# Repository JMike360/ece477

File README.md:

# ece477
Purdue ECE senior design project of team 8 for Fall 2020  
  
## Team members
John Michael Bolinder (Team leader, software engineer, systems engineer)  
Ethan Rodriguez (Systems engineer, secondary software engineer)  
Jiahui Zhu (Software engineer, secondary hardware engineer)  
Andrew Gan (Hardware engineer, secondary systems engineer)  

## Overview
Skeleton Key is a convenient, fully-featured password management solution, completely client-side with no dependence on a cloud service provider or network connection. The device utilizes an ESP32 microcontroller and onboard peripherals to manage encrypted-at-rest password storage, fingerprint-based authentication for easy and secure access to passwords, and interfaces with a client desktop app to wirelessly retrieve passwords via bluetooth or retrieve passwords through a wired USB connection. Passwords transmitted by USB or Bluetooth are encrypted in-flight, and the desktop application provides easy access to passwords on the target user device.
  
## Tools used
USB URT module  
ESP32  
Fingerprint reader  
SD card  
SD card reader  
LCD module  
  
## GPIO table
| GPIO PIN      | Function  | Endpoint     |
|---------------|-----------|--------------|
| 1             | U0TXD     | FT232 RXD    |
| 3             | U0RXD     | FT232 TXD    |
| 9             | U1RXD     | Console in   |
| 10            | U1TXD     | Console_out  |
| 12            | HSPI_MISO | MicroSD Dout |
| 13            | HSPI_MOSI | MicroSD Din  |
| 14            | HSPI_CLK  | MicroSD CLK  |
| 15            | HSPI_CS0  | MicroSD CS   |
| 16            | U2RXD     | Fingerprint Scanner TX |
| 17            | U2TXD     | Fingerprint Scanner RX |
  
UART 0: console/debug  
UART 1: ESP32 - GUI  
UART 2: ESP32 - Fingerprint  
  
GPIO 6-11 - SPI flash  
GPIO 34-39 - input mode only    
[Full layout](https://microcontrollerslab.com/wp-content/uploads/2019/02/ESP32-pinout-mapping.png)  
ESP32 tech ref manual page 57-58  
  
## References
[ESP32 SPI MASTER API](https://docs.espressif.com/projects/esp-idf/en/latest/esp32/api-reference/peripherals/spi_master.html)

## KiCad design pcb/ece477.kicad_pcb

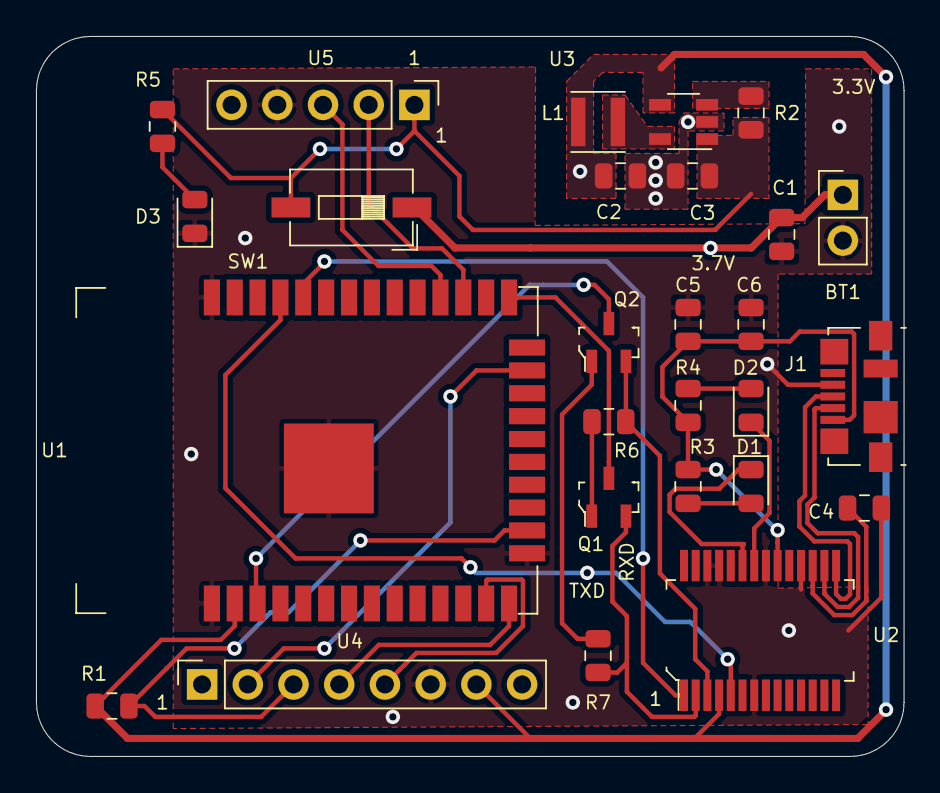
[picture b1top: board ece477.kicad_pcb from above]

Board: 2 copper layers, 48.2 x 40.0 mm, 27 parts (0 on the bottom side), 29 nets.

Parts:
BT1: 3.7V; PinHeader_1x02_P2.54mm_Vertical
C1, C3: 4.7µF; C_0805_2012Metric
C2: 10µF; C_0805_2012Metric
C4, C5: 0.1uF; C_0805_2012Metric
C6: 10uF; C_0805_2012Metric
D1, D2, D3: LED; LED_0805_2012Metric
J1: USB_B; USB_Micro-B_Molex_47346-0001
L1: 2.2µH; IND_LQH3NPN2R2MMEL
Q1, Q2: MMBT2222; SOT-23-3
R1, R2: 10kΩ; R_0805_2012Metric
R3, R4: 500Ω; R_0805_2012Metric
R5, R6, R7: 1kΩ; R_0805_2012Metric
SW1: SW_DIP_x01; SW_DIP_SPSTx01_Slide_6.7x4.1mm_W6.73mm_P2.54mm_LowProfile_J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
U1: ESP32-WROOM-32; ESP32-WROOM-32D
U2: FT232RL-REEL; SSOP-28_W5.30mm
U3: LM3671; TSOT-23-5
U4: ADA254; PinSocket_1x08_P2.54mm_Vertical
U5: ADA751; PinHeader_1x05_P2.54mm_Vertical

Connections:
GND: BT1.2, C1.1, C2.1, C3.1, C4.1, C5.2, C6.2, D3.1, J1.4, U1.1, U1.15, U1.38, U1.39, U2.7, U2.18, U2.21, U2.25, U2.26, U3.2, U4.6, U5.4
unnamed: BT1.1, C1.2, SW1.1
unnamed: C2.2, L1.1, R1.1, U1.2, U2.4, U3.4, U4.7
unnamed: C3.2, R2.2, R5.1, SW1.2, U3.1, U5.1
unnamed: C4.2, U2.17
unnamed: C5.1, C6.1, J1.1, R3.1, R4.1, U2.20
unnamed: D1.1, U2.23
unnamed: D1.2, R3.2
unnamed: D2.1, U2.22
unnamed: D2.2, R4.2
unnamed: D3.2, R5.2
unnamed: J1.2, U2.16
unnamed: J1.3, U2.15
unnamed: L1.2, U3.5
unnamed: Q1.1, R6.1
unnamed: Q1.2, R7.2, U2.2
unnamed: Q1.3, U1.25
unnamed: Q2.1, R7.1
unnamed: Q2.2, R6.2, U2.3
unnamed: Q2.3, U1.3
unnamed: R1.2, U1.16, U4.3
unnamed: R2.1, U3.3
unnamed: U1.13, U4.5
unnamed: U1.14, U4.4
unnamed: U1.23, U4.2
unnamed: U1.27, U5.2
unnamed: U1.28, U5.3
unnamed: U1.34, U2.1
unnamed: U1.35, U2.5

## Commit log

2020-09-03 tidy up README
2020-09-03 added FatFS files
2020-09-03 removed docs
2020-09-03 edit README
2020-09-03 Update README.md
    added new part
2020-09-04 added more references
2020-09-04 added example code
2020-09-04 removed sdinit.jpg
2020-09-05 setup gpio reservation table
2020-09-05 added oled folder
2020-09-05 grouped HSPI buses together
2020-09-06 oled init and cmds
2020-09-06 added pcb
2020-09-07 debug oled
2020-09-07 debug SPI
2020-09-07 removed misc files
2020-09-08 adding oled for SMAT
2020-09-09 used a new way to convert data to SPI ready
2020-09-09 include function to convert uint to SPI format
2020-09-09 added reference
2020-09-15 Update README.md
    Added gpio/pin request
2020-09-15 added fingerprint scanner pins
2020-09-16 template app with crypto tests and uart tests for fingerprint sensor
2020-09-17 sd card init success
2020-09-17 Add files via upload
    Demo Template so far for software application.
    Still need to discuss library and functionality
    Help button will link to user manual,
    Project website will link to the ECE 477 team page.
    Connect Device will help users figure out if their device is connected and if they can access the device from the application.
    User Settings will allow a user to put information, put a their fingerprint (cute gif animation and status bar to be added), and have an emergency pin that will reset the device (maybe)
2020-09-17 Add files via upload
    CORRECT UPLOAD FOLDER
    Demo Template so far for software application.
    Still need to discuss library and functionality
    Help button will link to user manual,
    Project website will link to the ECE 477 team page.
    Connect Device will help users figure out if their device is connected and if they can access the device from the application.
2020-09-18 added sd func
2020-09-18 cleared build files
2020-09-18 connected fingerprint scanner in schematic
2020-09-19 added sd card, battery and esp32 qfn to pcb
2020-09-19 updated pcb
2020-09-19 added wires to pcb
2020-10-06 removed deleteme folder
2020-10-06 Added fingerprint files
2020-10-07 cleanup
2020-10-07 uploaded pcb files
2020-10-08 slight pcb changes
2020-10-08 squeezed lm3671 components together
2020-10-08 pcb update
2020-10-08 shifted LM3671 to top right
2020-10-09 some fixes not done yet
2020-10-09 updated C and R size, fixed LM3671
2020-10-10 connected to ground plate
2020-10-11 added power LED
2020-10-12 fixed LM3671 ground vias
2020-10-14 updated pcb pinheader width
2020-10-15 gui-blink added
2020-10-16 script to make led work
2020-10-17 updated pcb with programming transistors
2020-10-21 pcb final touch
2020-10-22 added uart cmd
2020-10-22 manifest.c
2020-10-22 manifest processing
2020-10-22 added amnifest
2020-10-23 store and retrieve credentials
2020-10-24 tested manifest and sd rw functions, merged sd into final
2020-10-28 added function description
2020-10-29 Add files via upload
    So far trouble shooting request creds and entries.
    Can do LEDS and Make creds.
    After finishing the request creds/entries, then it be delete for the sd protocols.
    Please for testing go to connections, and go to USB
2020-10-29 updated console output uart num
2020-10-29 updated GPIO pin usage on readme
2020-10-29 tested GUI SD card
2020-11-04 merging uart with bluetooth
2020-11-05 integrated bluetooth, pending testing
2020-11-10 bluetooth testing complete
2020-11-12 Updated fingerprint sensor driver library
2020-11-17 fp sensor driver updates - file download and key generation now complete, additional fixes to sendPacketAsByteStream size calculation
2020-11-17 Added additional led ctrl functions
2020-11-17 added interface for high level fp sensor functions
2020-11-17 added high level function implementations, with tests in main.c
2020-11-17 added more led turn off commands
2020-11-17 integration completed pending testing
2020-11-19 integrating rsa
2020-11-20 Add files via upload
    Fingerprint scanner, and fixed layout
2020-11-21 fingerprint authentication complete
2020-11-22 user given 3 tries for matching fingerprint
2020-11-22 testing aes
2020-11-22 AES integration complete
2020-11-24 clear SD data upon fingerprint enrollment
2020-11-24 fixed some decrypt bugs
2020-11-24 Add files via upload
    Eveerything but autofill websites should work
2020-11-26 implemented ESP32-side RSA keygen and exchange, encryption and decryption
2020-11-26 untested functions for two way rsa key exchange
2020-11-30 cleanup comment
2020-12-01 tested RSA pub key exchange
2020-12-01 fixing RSA import
2020-12-01 RSA pub key exchange success
2020-12-01 GUI code
2020-12-01 Added connection mode processing from the sd card interface form to the fingerprint management form
2020-12-01 minor fixes to Form 3
2020-12-01 removed auth check for data wipe
2020-12-01 wait for connection before fingerprint authentication
2020-12-01 reverting to prev commit
2020-12-01 fixed manifest clearing
2020-12-01 minor fix
2020-12-02 attempting to fix RSA formatting issues
2020-12-02 patched crypto and removed rsa
2020-12-02 tested UART before checkoff
2020-12-02 creating third branch for RSA
2020-12-02 added ESP32-side RSA
2020-12-02 RSA updated
2020-12-03 added send key upon BT pairing
2020-12-03 fixed padding issue
2020-12-03 Revert "added send key upon BT pairing"
    This reverts commit 857cb985afd17799fd5dff5fa37e404728a60f81.
2020-12-03 Revert "Revert "added send key upon BT pairing""
    This reverts commit 9c458bcb98b68cc03867c657270fbcf0ae9dc0a6.
2020-12-03 Revert "fixed padding issue"
    This reverts commit 6a697a22eb476a6b2bc77f968b9bfb3fd9c18767.
2020-12-03 fixes for rsa key exchange
2020-12-03 ESP32 receive key
2020-12-03 fixes for receiving gui's public key
2020-12-03 properly disconnect BT
2020-12-03 return null when no entries found
2020-12-03 added some debug log
2020-12-03 some fix
2020-12-03 resolving doCMD free
2020-12-03 minor change to my_rsa
2020-12-03 using RSA functions that account for padding
2020-12-03 print err code
2020-12-03 changed sd card CLK gpio pin to fix flash-time and boot-time interference
2020-12-04 minor change
2020-12-04 esp32 test encrypt
2020-12-04 changed output format for encrypted hex
2020-12-04 more testing, got decryption to work for only request entries (from gui)
2020-12-04 add null term
2020-12-04 fix print
2020-12-04 write after storing/deleting cred
2020-12-04 added rsa complete
2020-12-04 lots of gui changes to enable RSA
2020-12-04 fix BT disconnect
2020-12-04 print to check if key changed
2020-12-04 somehow got esp-side-encrypt/gui-side-decrypt working
2020-12-04 it's actually working omg im gonna cry
